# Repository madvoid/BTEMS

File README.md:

# BTEMS
This is the repository for the BTEMS Sensor Stations. A majority of the documentation is in this file, but some is in the code.

### Uploading Instructions
First, change the `XX` in the filename on line 26 to whatever the BTEMS identifier code is. The current methodology is to use a two digit hexadecimal number. Then, using a 3.3v FTDI programmer such as [this](https://www.adafruit.com/products/284) or [this](https://www.sparkfun.com/products/9873), upload BTEMS.ino to a BTEMS. In the Arduino IDE 'tools' menu, the board should be set to `Arduino Pro or Pro Mini`, the processor should be set to `ATmega328 (3.3V, 8Mhz)`, and the programmer should be set to whatever programmer is used. `AVRISP mkll` often works. The port should be set to whatever port the Arduino is plugged into. The power switch on the BTEMS should be set to off when programming.

### Running Instructions
Place the BTEMS where measurements should take place. Ensure there's an SD card inserted into the SD slot. Turn the switch from 'OFF' to 'ON'. After ~3 seconds, the green LED will turn on and remain lit for ~2 seconds. From then on, the BTEMS is running. The green LED should blink every ~10 seconds, implying a measurement was taken. If a red light comes on after turning on, the likely culprit is either the SD card or the real time clock. Make sure the SD card works and has space, and make sure the real time clock works and has a backup battery plugged in.

To turn off, wait until the green LED blinks, then turn the switch from 'ON' to 'OFF' soon after. It is important to wait until the LED is finished blinking to make sure the file is successfully saved.

### File Descriptions
* BTEMS/
 * `BTEMS.ino` - BTEMS arduino sketch
 * `SHT2x.h` - SHT21 library header
 * `SHT2x.cpp` - SHT21 library file
* BTEMS PCB/
 * `BTEMS.brd` - Eagle board file for BTEMS PCB
 * `BTEMS.sch` - Eagle schematic file for BTEMS PCB
 * `BTEMS.*.ger` - BTEMS gerber files for manufacturing
 * `BTEMS.*.xln` - More BTEMS manufacturing files
 * `eagle.epf` - Eagle preferences file
* Data Sheets/
 * Contain part data sheets for posterity
* Matlab Scripts/
 * `Battery_Analysis.m` - Estimates the battery life given certain assumptions.
 * `BTEMS_Plotter.m` - Requests a BTEMS output .csv file from the user and plots some common plots. Very simple
* Radiation Shield/
 * `Radiation_Shield_RevD.*` - The CAD files for the radiation shield. Edit the .SLDPRT file, submit the .STL file for 3D printing, and view the .pdf file. The .STL file can be easily previewed within Github.
 * `SHT_Plug.*` - The CAD files for the plug that holds the SHT21. Edit the .SLDPRT file, submit the .STL file for 3D printing, and view the .pdf file. The .STL file can be easily previewed within Github
* `Bill of Materials.xlsx` - BTEMS bill of materials. Should be 99.9% complete. Missing any mounting hardware or insulation materials.

### Troubleshooting
* Red Light: SD card problem. Is there an SD card? Is it working? Is it formatted? 
 * In one instance, one of the batteries leaked, leaving residue all over the battery holder. The unit would turn on, but a new file would not be able to be created, and the red light would show. After cleaning the residue and replacing the batteries, the unit worked. It is suspected that the residue limited the amount of current available to the unit, which prevented the SD card from working properly.
* No Lights: Possible sensor problem. Are they plugged in? Are they good? Are they plugged in backwards?

### To-Do
1. Measurement validation

### Notes
* Heat ruins the battery life. Outdoor BTEMS will perform poorly compared to the indoor ones.

### Assembly Instructions
1. Solder SD card holder to PCB
2. Solder female RTC header to PCB
3. Solder four male header pins to RTC in the PWR, GND, SCL, SDA holes
4. Solder resistors in corect place
5. Solder power switch in place
6. Solder power screw terminal in place. Make sure screw terminal is straight and fits flush on the PCB!
7. Solder Arduino in place. The programming header on the Arduino should be near on the side of the power switch. Use regular male headers, and the long side of the headers should be pointing up from the board. Make sure all the pins on the Arduino, especially the four pins in the middle of the arduino, are passed through to the PCB.
8. Solder male headers for sensor plug ins in place
   Detail to be added...

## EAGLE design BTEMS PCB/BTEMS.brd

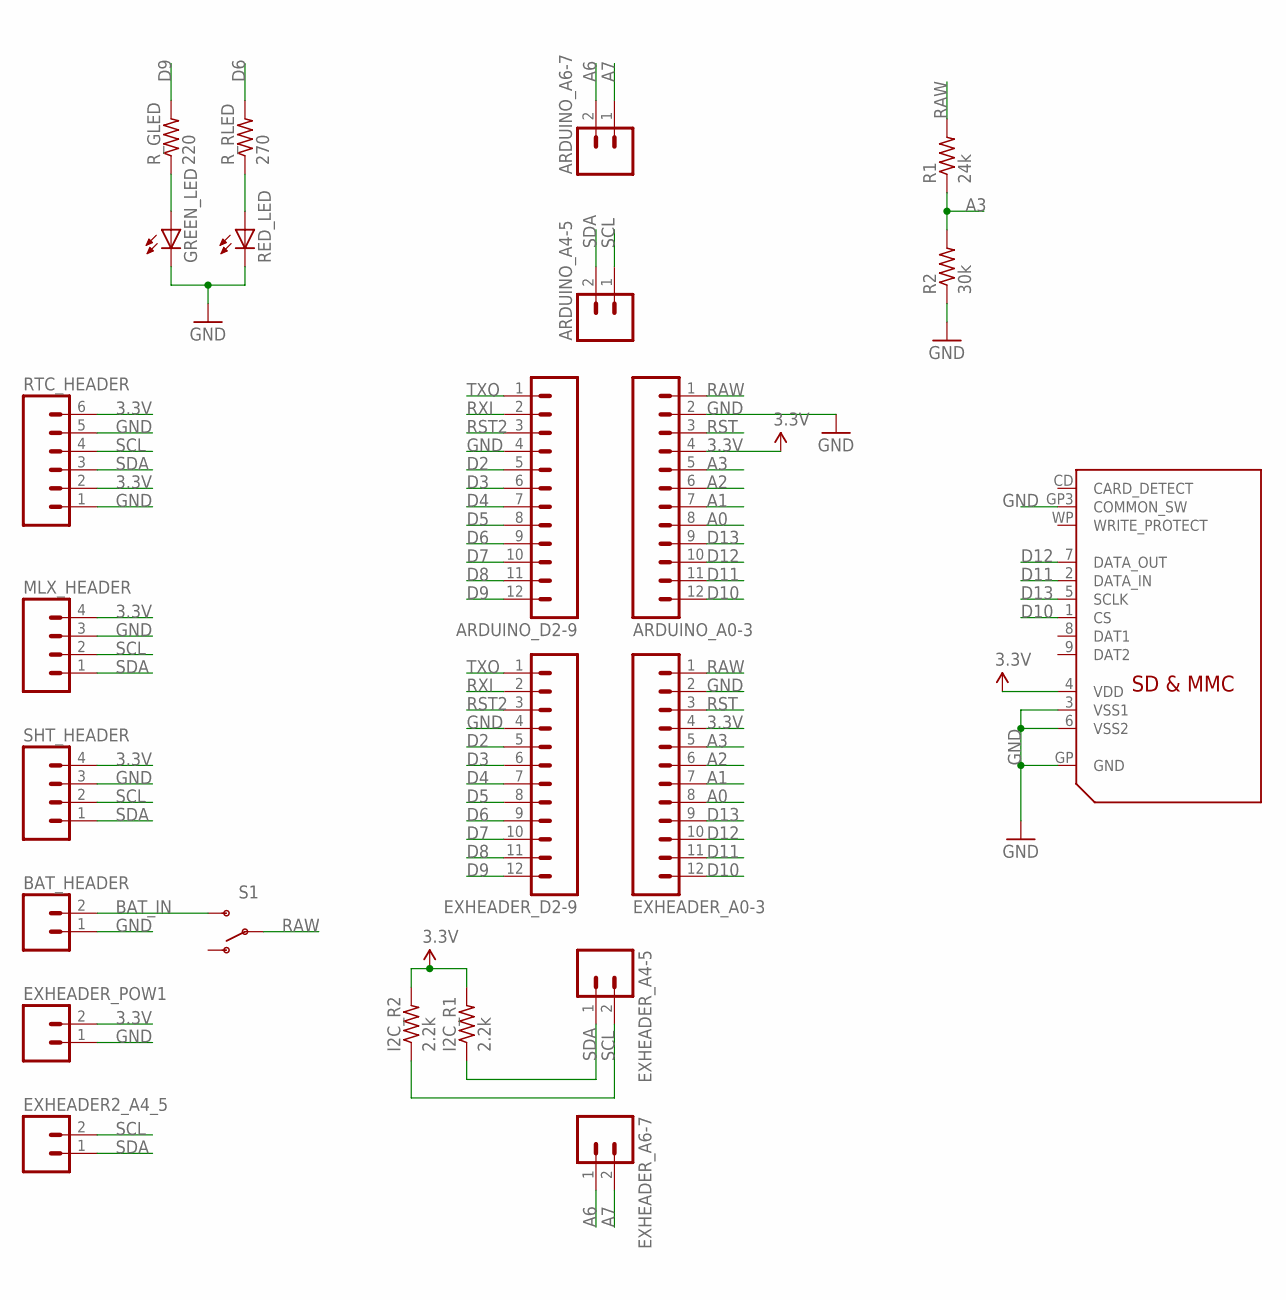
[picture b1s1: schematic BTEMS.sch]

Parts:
ARDUINO_A0-3: M12LOCK; 1X12_LOCK
ARDUINO_A4-5, ARDUINO_A6-7: M02PTH; 1X02
ARDUINO_D2-9: M12LOCK; 1X12_LOCK
BAT_HEADER: M023.5MM; SCREWTERMINAL-3.5MM-2
EXHEADER2_A4_5: M02PTH; 1X02
EXHEADER_A0-3: M12PTH; 1X12
EXHEADER_A4-5, EXHEADER_A6-7: M02LOCK; 1X02_LOCK
EXHEADER_D2-9: M12PTH; 1X12
EXHEADER_POW1: M02PTH; 1X02
GREEN_LED: LED3MM
I2C_R1, I2C_R2: 2.2k; 0207/7
MLX_HEADER: M04LOCK; 1X04_LOCK
R1: 24k; 0207/7
R2: 30k; 0207/7
RED_LED: LED3MM
RTC_HEADER: M06FEMALE_LOCK; 1X06_FEMALE_LOCK.010
R_GLED: 220; 0207/7
R_RLED: 270; 0207/7
S1: SWITCH-SPDTPTH; SWITCH-SPDT
SDSLOT: SDMMC06132; 06132
SHT_HEADER: M04LOCK; 1X04_LOCK

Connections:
3.3V: ARDUINO_A0-3.4, EXHEADER_A0-3.4, EXHEADER_POW1.2, I2C_R1.2, I2C_R2.2, MLX_HEADER.4, RTC_HEADER.2, RTC_HEADER.6, SDSLOT.4 (VDD), SHT_HEADER.4
A0: ARDUINO_A0-3.8, EXHEADER_A0-3.8
A1: ARDUINO_A0-3.7, EXHEADER_A0-3.7
A2: ARDUINO_A0-3.6, EXHEADER_A0-3.6
A3: ARDUINO_A0-3.5, EXHEADER_A0-3.5, R1.1, R2.2
A6: ARDUINO_A6-7.2, EXHEADER_A6-7.1
A7: ARDUINO_A6-7.1, EXHEADER_A6-7.2
BAT_IN: BAT_HEADER.2, S1.3 (S)
D2: ARDUINO_D2-9.5, EXHEADER_D2-9.5
D3: ARDUINO_D2-9.6, EXHEADER_D2-9.6
D4: ARDUINO_D2-9.7, EXHEADER_D2-9.7
D5: ARDUINO_D2-9.8, EXHEADER_D2-9.8
D6: ARDUINO_D2-9.9, EXHEADER_D2-9.9, R_RLED.2
D7: ARDUINO_D2-9.10, EXHEADER_D2-9.10
D8: ARDUINO_D2-9.11, EXHEADER_D2-9.11
D9: ARDUINO_D2-9.12, EXHEADER_D2-9.12, R_GLED.2
D10: ARDUINO_A0-3.12, EXHEADER_A0-3.12, SDSLOT.1 (CS)
D11: ARDUINO_A0-3.11, EXHEADER_A0-3.11, SDSLOT.2 (DATA_IN)
D12: ARDUINO_A0-3.10, EXHEADER_A0-3.10, SDSLOT.7 (DATA_OUT)
D13: ARDUINO_A0-3.9, EXHEADER_A0-3.9, SDSLOT.5 (SCLK)
GND: ARDUINO_A0-3.2, ARDUINO_D2-9.4, BAT_HEADER.1, EXHEADER_A0-3.2, EXHEADER_D2-9.4, EXHEADER_POW1.1, GREEN_LED.K (C), MLX_HEADER.3, R2.1, RED_LED.K (C), RTC_HEADER.1, RTC_HEADER.5, SDSLOT.3 (VSS1), SDSLOT.6 (VSS2), SDSLOT.GP (GND), SDSLOT.GP3 (COMMON_SW), SHT_HEADER.3
unnamed: GREEN_LED.A, R_GLED.1
unnamed: RED_LED.A, R_RLED.1
RAW: ARDUINO_A0-3.1, EXHEADER_A0-3.1, R1.2, S1.2
RST: ARDUINO_A0-3.3, EXHEADER_A0-3.3
RST2: ARDUINO_D2-9.3, EXHEADER_D2-9.3
RXI: ARDUINO_D2-9.2, EXHEADER_D2-9.2
SCL: ARDUINO_A4-5.1, EXHEADER2_A4_5.2, EXHEADER_A4-5.2, I2C_R2.1, MLX_HEADER.2, RTC_HEADER.4, SHT_HEADER.2
SDA: ARDUINO_A4-5.2, EXHEADER2_A4_5.1, EXHEADER_A4-5.1, I2C_R1.1, MLX_HEADER.1, RTC_HEADER.3, SHT_HEADER.1
TXO: ARDUINO_D2-9.1, EXHEADER_D2-9.1

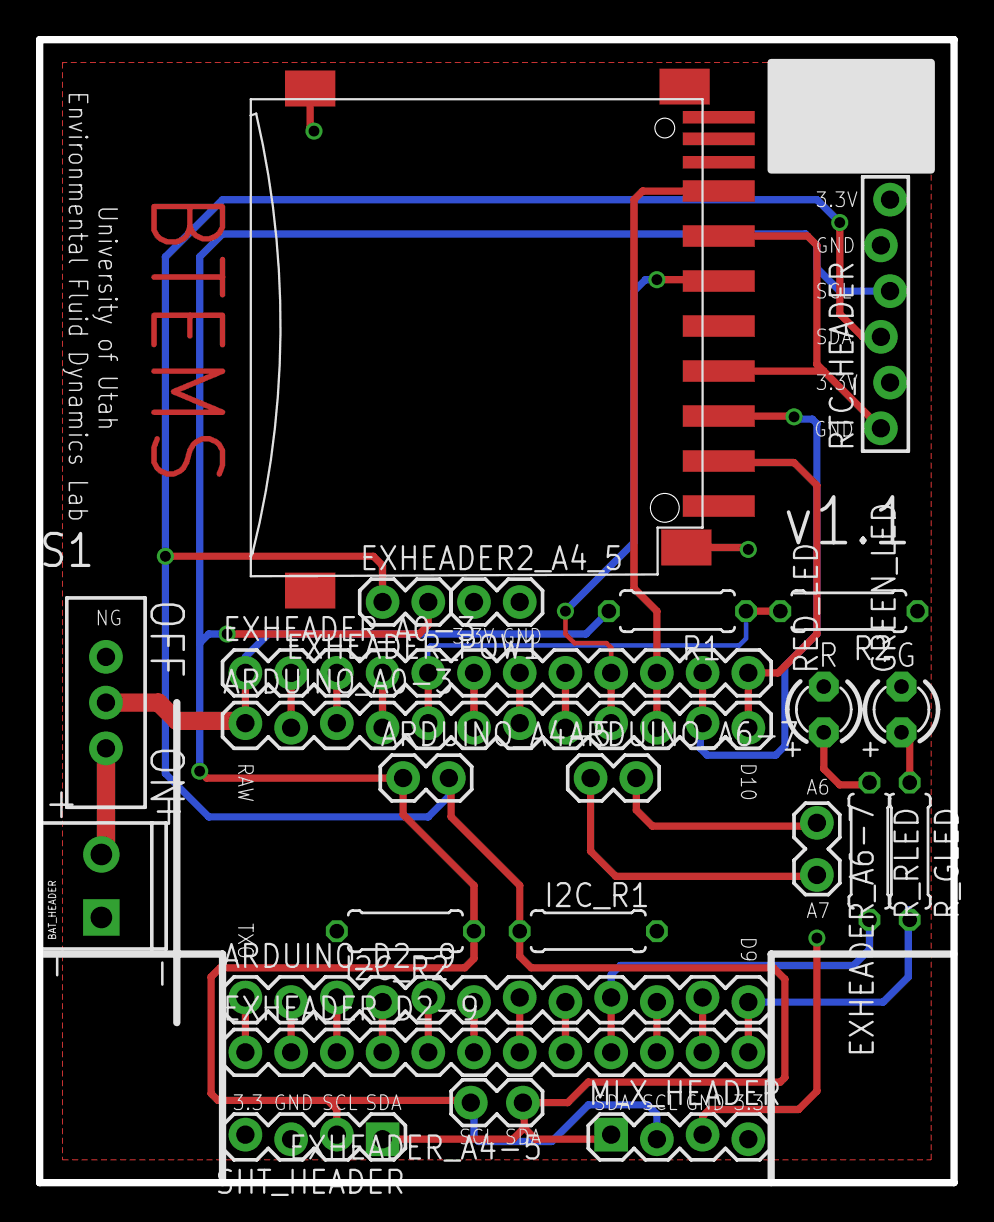
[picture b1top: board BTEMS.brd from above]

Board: 2 copper layers, 50.8 x 63.5 mm, 24 parts (0 on the bottom side), 30 nets.

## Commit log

2015-10-13 Added RTC code, cleaned up comments
2015-10-13 Added functions for LEDs
2016-01-29 Cleaned up code, added correct RTC lib
2016-02-06 Minor changes, added battery checking
2016-02-07 Added several files, minor changes
2016-02-08 Solidified part position, added BOM
2016-02-09 Routed board
2016-02-09 Added silkscreen, BOM parts
2016-02-09 Added battery voltage equation
2016-02-11 Many changes and added gerber files
2016-02-15 Osh Park Submission
2016-02-23 Minor todo changes
2016-02-24 Init mlxPin commit. Added untested MLX pow. switch
2016-02-25 Working mlx power switching
2016-02-25 Minor changes/Updated todo
2016-02-25 Todo additions
2016-02-26 v1.1 changes added
2016-02-28 v1.1 final, mostly finished BOM
2016-02-28 Modified todo
2016-03-08 Updated BOM
2016-03-19 Added todos
2016-04-04 Added plotter code, BTEMS file name changing
2016-04-05 Minor comment changes
2016-04-17 Added radiation shield parts
2016-04-17 Updated todo
2016-04-19 Added information to README, file reorganization
2016-05-05 Added data sheets
2016-05-24 Add data sheets, minor changes
2016-06-16 Update bill of materials
2016-06-21 Added schematic names to BOM
2016-06-22 Added info for 6-22-16 order
2016-06-23 Final commit before medium run PCB order
2016-06-23 Added PCB costs to BOM
2016-07-22 Minor notes added
2017-07-17 Moved SHT2x library to main code folder

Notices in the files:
parts and their libraries:
SparkFun-Connectors: Licensing: Creative Commons ShareAlike 4.0 International - https://creativecommons.org/licenses/by-sa/4.0
